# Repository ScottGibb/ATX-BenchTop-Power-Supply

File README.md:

# ATX-BenchTop-Power-Supply
Circuit diagram and Layout files for an ATX Bench Top open-source Power Supply

The circuit was created in Eagle using both through-hole and surface-mount components. The power supply board is developed such that it can use an old PC ATX power supply.
CAD design was done using Fusion 360 and will be available on thingiverse:

Thingiverse Link:
TBC

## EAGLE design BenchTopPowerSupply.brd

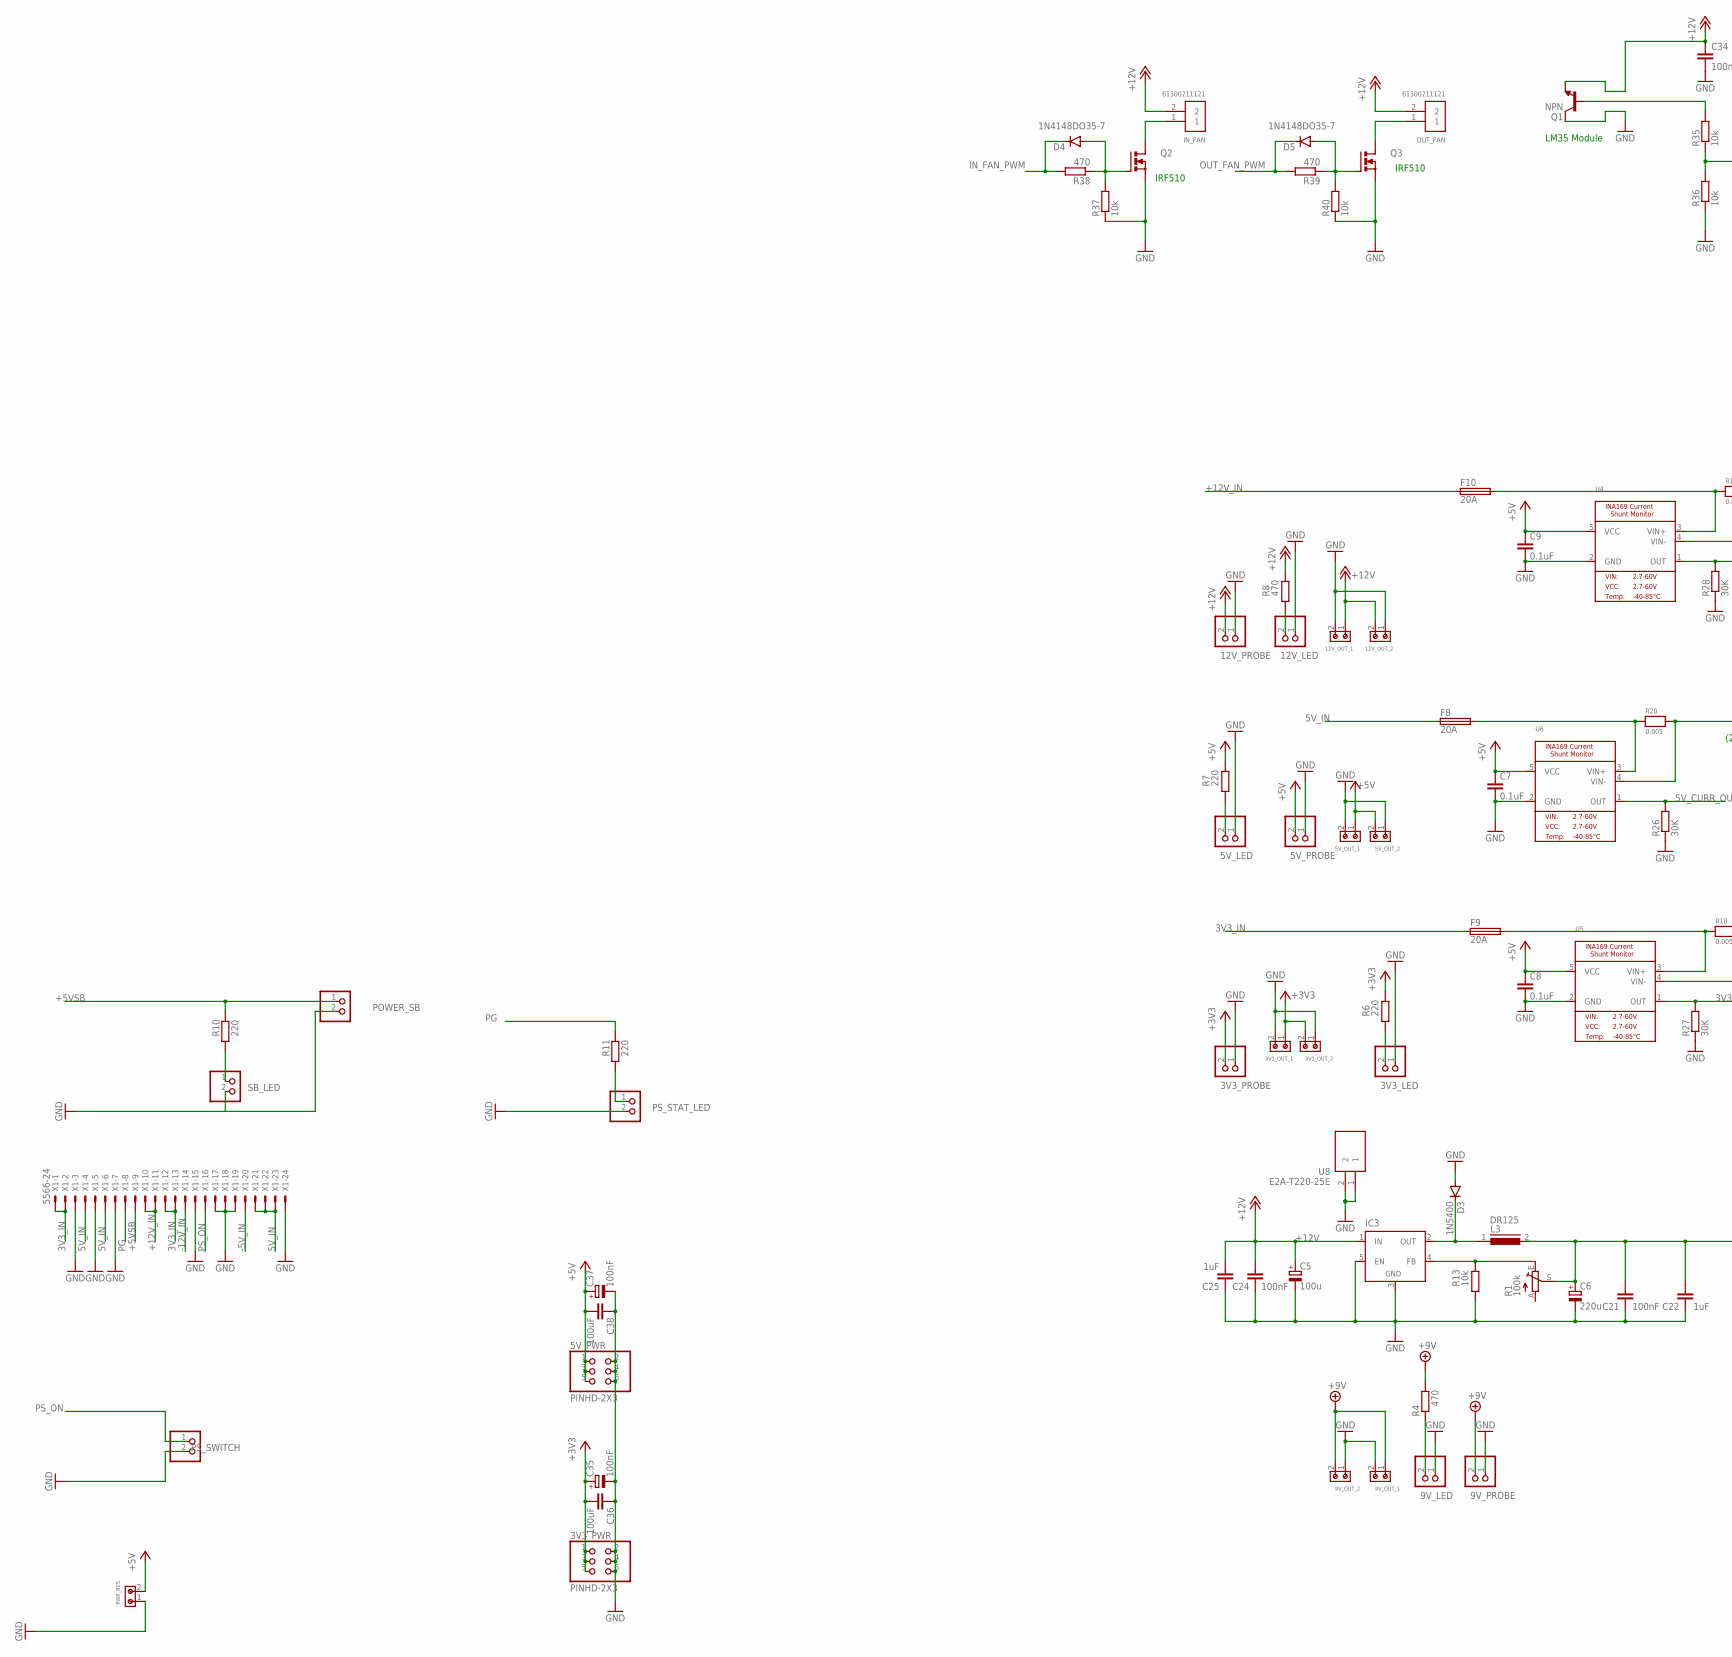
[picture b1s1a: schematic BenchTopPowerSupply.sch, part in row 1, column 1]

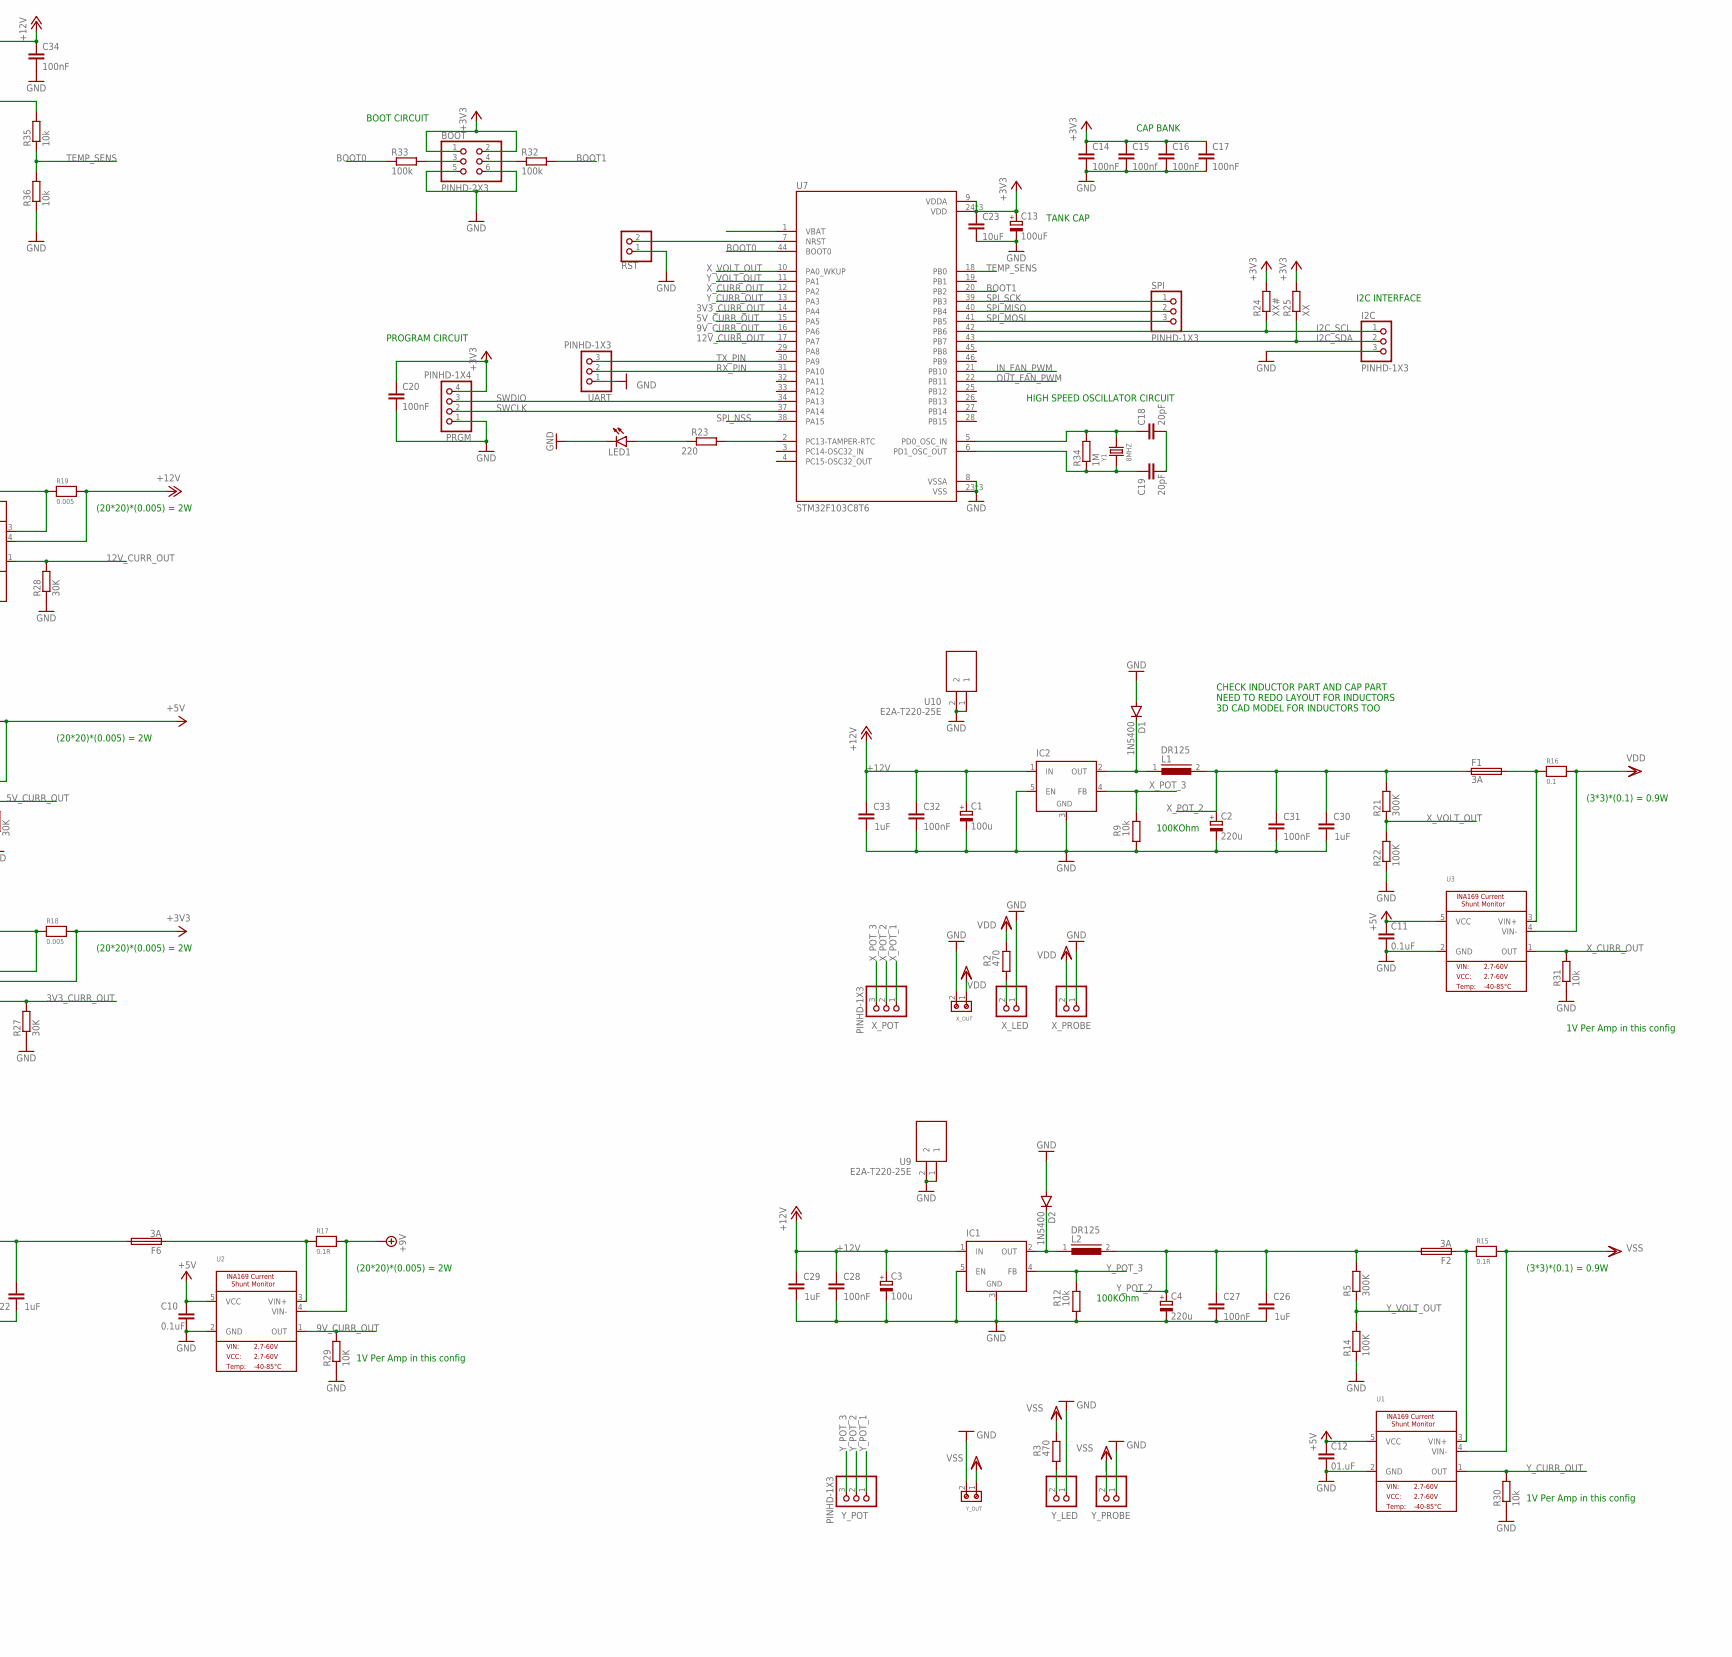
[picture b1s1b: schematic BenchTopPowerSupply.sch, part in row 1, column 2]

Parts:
3V3_LED, 3V3_PROBE, 5V_LED, 5V_PROBE, 9V_LED, 9V_PROBE, 12V_LED, 12V_PROBE: PINHD-1X2; 1X02
3V3_OUT_1, 3V3_OUT_2, 5V_OUT_1, 5V_OUT_2, 9V_OUT_1, 9V_OUT_2, 12V_OUT_1, 12V_OUT_2: 691216510002S
3V3_PWR, 5V_PWR: PINHD-2X3; 2X03
BOOT: PINHD-2X3; 2X03
C1, C3, C5: 100u; E5-10,5
C2, C4, C6: 220u; E5-10,5
C7, C8, C9, C10, C11: 0.1uF; C1206
C12: 01.uF; C1206
C13: 100uF; E5-5
C14, C16, C17, C20, C21, C24, C27, C28, C31, C32, C34: 100nF; C1206
C15: 100nf; C1206
C18, C19: 20pF; C1206
C22, C25, C26, C29, C30, C33: 1uF; C1206
C23: 10uF; C1206
C35, C37: 100nF; E5-5
C36, C38: 100uF; C1206
D1, D2, D3: 1N5400; DO201-15
D4, D5: 1N4148DO35-7; DO35-7
F1, F2, F6: 3A; SHK20L
F8, F9, F10: 20A; SHK20L
I2C: PINHD-1X3; 1X03
IC1, IC2, IC3: LM2596TV; TO220-51
IN_FAN: 61300211121
L1, L2, L3: DR125
LED1: LED5MM
OUT_FAN: 61300211121
POWER_SB: PINHD-1X2; 1X02
PRGM: PINHD-1X4; 1X04
PS_STAT_LED: PINHD-1X2; 1X02
PS_SWITCH: PINHD-1X2; 1X02
PWR_RES: 691216510002S
Q1: NPN; TO92
Q2, Q3: IRF510; TO220BV
R1: 100k; S64W
R2, R3, R4, R8, R38, R39: 470; R1206
R5, R21: 300K; R1206
R6, R7, R10, R11, R23: 220; R1206
R9, R12, R13, R30, R31, R35, R36, R37, R40: 10k; R1206
R14, R22: 100K; R1206
R15, R17: 0.1R; RESC6335X60N
R16: 0.1; RESC6335X60N
R18, R19, R20: 0.005; RESC6335X60N
R24: XX#; R1206
R25: XX; R1206
R26, R27, R28: 30K; R1206
R29: 10K; R1206
R32, R33: 100k; R1206
R34: 1M; R1206
RST: PINHD-1X2; 1X02
SB_LED: PINHD-1X2; 1X02
SPI: PINHD-1X3; 1X03
U1, U2, U3, U4, U5, U6: MICROBUILDER_INA1693D_PACKAGE; SOT95P240X110-5N
U7: STM32F103C8T6; QFP50P900X900X160-48N
U8, U9, U10: E2A-T220-25E; E2AT22025E
UART: PINHD-1X3; 1X03
X1: 5566-24
X_LED: PINHD-1X2; 1X02
X_OUT: 691216510002S
X_POT: PINHD-1X3; 1X03
X_PROBE: PINHD-1X2; 1X02
Y1: 8MHZ; HC49US
Y_LED: PINHD-1X2; 1X02
Y_OUT: 691216510002S
Y_POT: PINHD-1X3; 1X03
Y_PROBE: PINHD-1X2; 1X02

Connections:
2B: F2.1A, R15.1, U1.3 (VIN+)
3V3_CURR_OUT: R27.2, U5.1 (OUT), U7.14 (PA4)
3V3_IN: F9.1A, X1.1, X1.2, X1.12, X1.13
5V_CURR_OUT: R26.2, U6.1 (OUT), U7.15 (PA5)
5V_IN: F8.1A, X1.4, X1.6, X1.21, X1.22, X1.23
9V_CURR_OUT: R29.2, U2.1 (OUT), U7.16 (PA6)
12V_CURR_OUT: R28.2, U4.1 (OUT), U7.17 (PA7)
+3V3: 3V3_OUT_1.1, 3V3_OUT_2.2, 3V3_PROBE.2, 3V3_PWR.1, 3V3_PWR.3, 3V3_PWR.5, BOOT.1, BOOT.2, C13.+, C14.1, C15.1, C16.1, C17.1, C20.1, C23.1, C35.+, C36.2, PRGM.4, R6.2, R18.2, R24.2, R25.2, U5.4 (VIN-), U7.9 (VDDA), U7.24 (VDD), U7.36 (VDD), U7.48 (VDD)
+5V: 5V_OUT_1.1, 5V_OUT_2.2, 5V_PROBE.2, 5V_PWR.1, 5V_PWR.3, 5V_PWR.5, C7.1, C8.1, C9.1, C10.1, C11.1, C12.1, C37.+, C38.2, PWR_RES.2, R7.2, R20.2, U1.5 (VCC), U2.5 (VCC), U3.5 (VCC), U4.5 (VCC), U5.5 (VCC), U6.4 (VIN-), U6.5 (VCC)
+5VSB: POWER_SB.1, R10.2, X1.9
+9V: 9V_OUT_1.1, 9V_OUT_2.2, 9V_PROBE.2, R4.2, R17.2, U2.4 (VIN-)
+12V: 12V_OUT_1.1, 12V_OUT_2.2, 12V_PROBE.2, C1.+, C3.+, C5.+, C24.2, C25.2, C28.2, C29.2, C32.2, C33.2, C34.1, IC1.1 (IN), IC2.1 (IN), IC3.1 (IN), IN_FAN.2, OUT_FAN.2, Q1.1 (E), R8.2, R19.2, U4.4 (VIN-)
+12V_IN: F10.1A, X1.10, X1.11
-5V_IN: X1.20
-12V_IN: X1.14
BOOT0: R33.1, U7.44 (BOOT0)
BOOT1: R32.2, U7.20 (PB2)
GND: 3V3_LED.1, 3V3_OUT_1.2, 3V3_OUT_2.1, 3V3_PROBE.1, 3V3_PWR.2, 3V3_PWR.4, 3V3_PWR.6, 5V_LED.1, 5V_OUT_1.2, 5V_OUT_2.1, 5V_PROBE.1, 5V_PWR.2, 5V_PWR.4, 5V_PWR.6, 9V_LED.1, 9V_OUT_1.2, 9V_OUT_2.1, 9V_PROBE.1, 12V_LED.1, 12V_OUT_1.2, 12V_OUT_2.1, 12V_PROBE.1, BOOT.5, BOOT.6, C1.-, C2.-, C3.-, C4.-, C5.-, C6.-, C7.2, C8.2, C9.2, C10.2, C11.2, C12.2, C13.-, C14.2, C15.2, C16.2, C17.2, C20.2, C21.1, C22.1, C23.2, C24.1, C25.1, C26.1, C27.1, C28.1, C29.1, C30.1, C31.1, C32.1, C33.1, C34.2, C35.-, C36.1, C37.-, C38.1, D1.A, D2.A, D3.A, I2C.3, IC1.3 (GND), IC1.5 (EN), IC2.3 (GND), IC2.5 (EN), IC3.3 (GND), IC3.5 (EN), LED1.K (C), POWER_SB.2, PRGM.1, PS_STAT_LED.2, PS_SWITCH.2, PWR_RES.1, Q1.3 (C), Q2.S, Q3.S, R9.1, R12.1, R13.1, R14.1, R22.1, R26.1, R27.1, R28.1, R29.1, R30.1, R31.1, R36.1, R37.1, R40.1, RST.1, SB_LED.2, U1.2 (GND), U2.2 (GND), U3.2 (GND), U4.2 (GND), U5.2 (GND), U6.2 (GND), U7.8 (VSSA), U7.23 (VSS), U7.35 (VSS), U7.47 (VSS), U8.1, U8.2, U9.1, U9.2, U10.1, U10.2, UART.1, X1.3, X1.5, X1.7, X1.15, X1.17, X1.18, X1.19, X1.24, X_LED.1, X_OUT.2, X_PROBE.1, Y_LED.1, Y_OUT.2, Y_PROBE.1
I2C_SCL: I2C.1, R24.1, U7.42 (PB6)
I2C_SDA: I2C.2, R25.1, U7.43 (PB7)
IN_FAN_PWM: D4.C, R38.2, U7.21 (PB10)
unnamed: D3.C, IC3.2 (OUT), L3.1
unnamed: IC3.4 (FB), R1.E, R13.2
unnamed: C18.1, R34.2, U7.5 (PD0_OSC_IN), Y1.2
unnamed: D1.C, IC2.2 (OUT), L1.1
unnamed: C19.1, R34.1, U7.6 (PD1_OSC_OUT), Y1.1
unnamed: F8.2A, R20.1, U6.3 (VIN+)
unnamed: R3.1, Y_LED.2
unnamed: R2.1, X_LED.2
unnamed: 9V_LED.2, R4.1
unnamed: C18.2, C19.2
unnamed: 3V3_LED.2, R6.1
unnamed: 5V_LED.2, R7.1
unnamed: 12V_LED.2, R8.1
unnamed: R10.1, SB_LED.1
unnamed: PS_STAT_LED.1, R11.1
unnamed: BOOT.4, R32.1
unnamed: C6.+, C21.2, C22.2, F6.2A, L3.2, R1.S
unnamed: D2.C, IC1.2 (OUT), L2.1
unnamed: F9.2A, R18.1, U5.3 (VIN+)
unnamed: F1.2A, R16.1, U3.3 (VIN+)
unnamed: F10.2A, R19.1, U4.3 (VIN+)
unnamed: F6.1A, R17.1, U2.3 (VIN+)
unnamed: RST.2, U7.7 (NRST)
unnamed: Q1.2 (B), R35.2
unnamed: R23.2, U7.2 (PC13-TAMPER-RTC)
unnamed: LED1.A, R23.1
unnamed: BOOT.3, R33.2
unnamed: D4.A, Q2.G, R37.2, R38.1
unnamed: IN_FAN.1, Q2.D
unnamed: D5.A, Q3.G, R39.1, R40.2
unnamed: OUT_FAN.1, Q3.D
OUT_FAN_PWM: D5.C, R39.2, U7.22 (PB11)
PG: R11.2, X1.8
PS_ON: PS_SWITCH.1, X1.16
RX_PIN: U7.31 (PA10), UART.2
SPI_MISO: SPI.2, U7.40 (PB4)
SPI_MOSI: SPI.3, U7.41 (PB5)
SPI_NSS: U7.38 (PA15)
SPI_SCK: SPI.1, U7.39 (PB3)
SWCLK: PRGM.2, U7.37 (PA14)
SWDIO: PRGM.3, U7.34 (PA13)
TEMP_SENS: R35.1, R36.2, U7.18 (PB0)
TX_PIN: U7.30 (PA9), UART.3
VDD: R2.2, R16.2, U3.4 (VIN-), X_OUT.1, X_PROBE.2
VSS: R3.2, R15.2, U1.4 (VIN-), Y_OUT.1, Y_PROBE.2
X_CURR_OUT: R31.2, U3.1 (OUT), U7.12 (PA2)
X_POT_1: X_POT.1
X_POT_2: C2.+, C30.2, C31.2, F1.1A, L1.2, R21.2, X_POT.2
X_POT_3: IC2.4 (FB), R9.2, X_POT.3
X_VOLT_OUT: R21.1, R22.2, U7.10 (PA0_WKUP)
Y_CURR_OUT: R30.2, U1.1 (OUT), U7.13 (PA3)
Y_POT_1: Y_POT.1
Y_POT_2: C4.+, C26.2, C27.2, F2.2A, L2.2, R5.2, Y_POT.2
Y_POT_3: IC1.4 (FB), R12.2, Y_POT.3
Y_VOLT_OUT: R5.1, R14.2, U7.11 (PA1)

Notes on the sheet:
CHECK INDUCTOR PART AND CAP PART NEED TO REDO LAYOUT FOR INDUCTORS 3D CAD MODEL FOR INDUCTORS TOO
BOOT CIRCUIT
PROGRAM CIRCUIT
HIGH SPEED OSCILLATOR CIRCUIT
I2C INTERFACE
CAP BANK
TANK CAP
1V Per Amp in this config
(20*20)*(0.005) = 2W
(3*3)*(0.1) = 0.9W
LM35 Module
IRF510
100KOhm

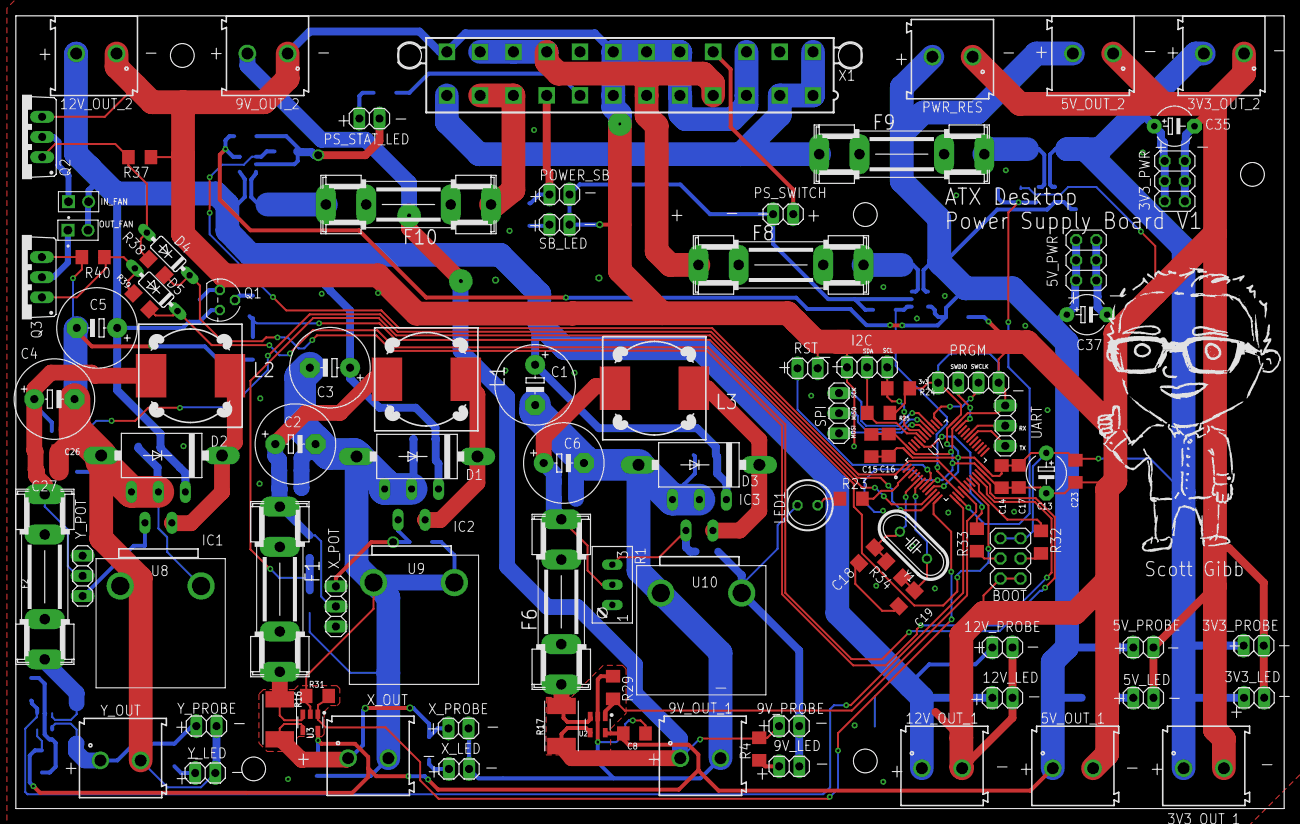
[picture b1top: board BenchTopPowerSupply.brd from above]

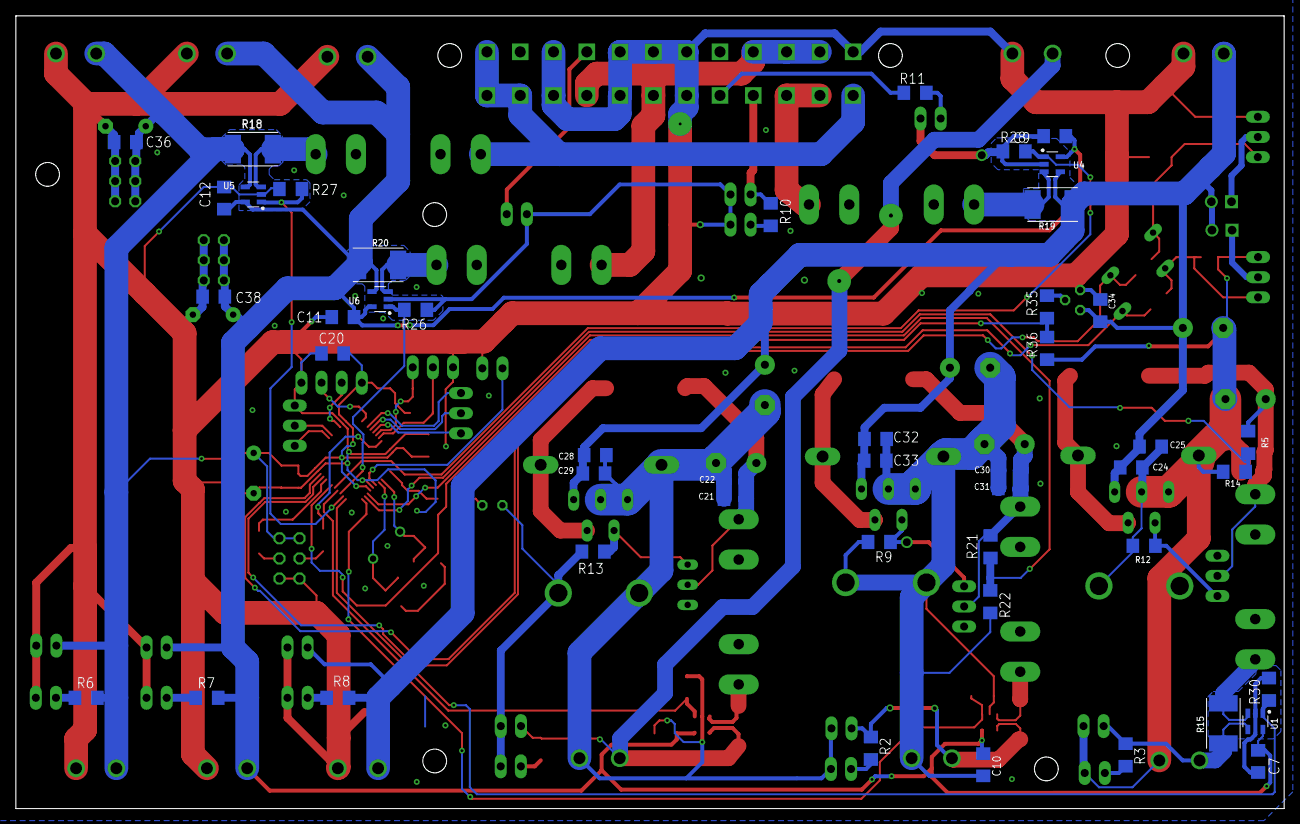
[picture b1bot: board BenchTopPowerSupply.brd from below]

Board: 2 copper layers, 160.0 x 100.0 mm, 150 parts (47 on the bottom side), 71 nets.

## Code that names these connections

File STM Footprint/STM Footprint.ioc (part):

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Mcu.UserName=STM32F103C8Tx
PA3.GPIOParameters=GPIO_Label
PA6.GPIO_Label=CURR_9V
PB0.GPIO_Label=TEMP_SENS
PB11.Signal=S_TIM2_CH4
PA2.GPIOParameters=GPIO_Label
PD1-OSC_OUT.Signal=RCC_OSC_OUT
PB6.Signal=I2C1_SCL
PB6.Mode=I2C
PA0-WKUP.GPIOParameters=GPIO_Label
PB3.Mode=Full_Duplex_Master
PA15.Mode=NSS_Signal_Hard_Output
PB0.GPIOParameters=GPIO_Label
PA1.GPIOParameters=GPIO_Label
PB4.Mode=Full_Duplex_Master
PA14.Mode=Serial_Wire
PB5.Mode=Full_Duplex_Master
PB7.Signal=I2C1_SDA
Mcu.Package=LQFP48
PA6.Signal=ADCx_IN6
PA2.GPIO_Label=CURR_X
PA10.Signal=USART1_RX
PA15.Signal=SPI1_NSS
PA5.GPIOParameters=GPIO_Label
PB10.GPIOParameters=GPIO_Label
PA4.GPIO_Label=CURR_3V3
PB4.Signal=SPI1_MISO
PA3.Signal=ADCx_IN3
PA6.GPIOParameters=GPIO_Label
PD1-OSC_OUT.Mode=HSE-External-Oscillator
PA10.Mode=Asynchronous
PB11.GPIO_Label=OUT_FAN_PWM
PC13-TAMPER-RTC.Signal=GPIO_Output
PD0-OSC_IN.Signal=RCC_OSC_IN
PA0-WKUP.GPIO_Label=VOLT_X
PA0-WKUP.Signal=ADCx_IN0
PA13.Signal=SYS_JTMS-SWDIO
PA9.Mode=Asynchronous
PB10.GPIO_Label=IN_FAN_PWM
PA9.Signal=USART1_TX
PB11.GPIOParameters=GPIO_Label
PA1.Signal=ADCx_IN1
PD0-OSC_IN.Mode=HSE-External-Oscillator
PB10.Signal=S_TIM2_CH3
PA5.Signal=ADCx_IN5
board=custom
PA1.GPIO_Label=VOLT_Y
PA4.GPIOParameters=GPIO_Label
PA13.Mode=Serial_Wire
Mcu.Name=STM32F103C(8-B)Tx
PA2.Signal=ADCx_IN2
PB3.Signal=SPI1_SCK
PA4.Signal=ADCx_IN4
PB5.Signal=SPI1_MOSI
PA7.GPIO_Label=CURR_12V
PA5.GPIO_Label=CURR_5V
PB7.Mode=I2C
PA14.Signal=SYS_JTCK-SWCLK
PB0.Signal=ADCx_IN8
PA7.GPIOParameters=GPIO_Label
PA3.GPIO_Label=CURR_Y
PA7.Signal=ADCx_IN7

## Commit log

2020-09-27 Adding Schematics, layout and CubeMX Files
2020-09-27 Adding ReadMe
2020-10-04 Fixing schematic issues
2020-10-17 Adding mounting holes to the design and experimenting with JLCPCB SMT assembly
2020-11-10 Changing to surface mount inductors, reduce noise on board, hopefully. Will need to redo layout however and figure out how to solder them
2020-11-10 updating layout silkskin, one final check then sending away for manufacture

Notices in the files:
parts and their libraries:
Wurth_Connectors_WR-TBL Rising Cage Clam: Copyright: Würth Elektronik
